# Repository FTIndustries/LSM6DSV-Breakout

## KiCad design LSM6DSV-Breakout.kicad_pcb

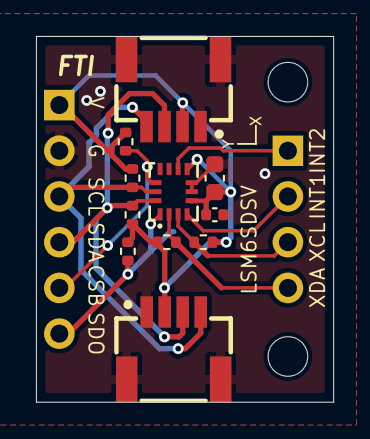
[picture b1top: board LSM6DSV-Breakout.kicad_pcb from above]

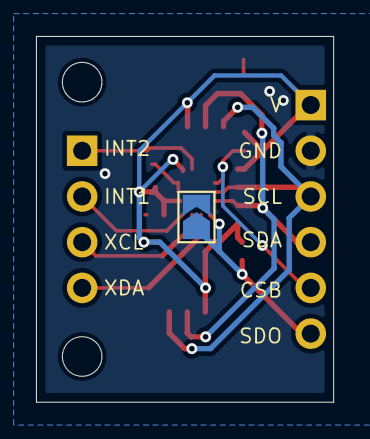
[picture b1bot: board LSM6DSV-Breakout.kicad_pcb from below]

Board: 2 copper layers, 16.5 x 20.3 mm, 16 parts (3 on the bottom side), 10 nets.

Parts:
C1: 1u; C_0603_1608Metric
C2: 100n; C_0402_1005Metric
CN1, CN2: AFC10-S04QCA-00; CONN-SMD_AFC10-S04QCA-00
H1, H2: MountingHole; MountingHole_2.2mm_M2
J1: Conn_01x06_Pin; PinHeader_1x06_P2.54mm_Vertical
J2: Conn_01x04_Pin; PinHeader_1x04_P2.54mm_Vertical
JP1: SolderJumper_2_Open; SolderJumper-2_P1.3mm_Open_TrianglePad1.0x1.5mm
R1, R2, R3, R4, R5, R6: 2.2k; R_0402_1005Metric
U1: LSM6DSVTR; LGA-14_L3.0-W2.5-P0.50-TL

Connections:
/CS: J1.5, R1.2, U1.12 (CS)
/INT1: J2.2, U1.4 (INT1)
/INT2: J2.1, U1.9 (INT2)
/SA0: J1.6, JP1.1 (A), R2.2, U1.1 (SDO/SA0)
/SCL: CN1.4, CN2.4, J1.3, R4.2, U1.13 (SCL)
/SDA: CN1.3, CN2.3, J1.4, R3.2, U1.14 (SDA)
/XCL: J2.3, R6.2, U1.3 (SCX)
/XDA: J2.4, R5.2, U1.2 (SDX)
GND: C1.2, C2.2, CN1.1, CN1.5, CN1.6, CN2.1, CN2.5, CN2.6, J1.2, JP1.2 (B), U1.6 (GND), U1.7 (GND)
VDD: C1.1, C2.1, CN1.2, CN2.2, J1.1, R1.1, R2.1, R3.1, R4.1, R5.1, R6.1, U1.5 (VDD_IO), U1.8 (VDD)

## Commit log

2024-04-23 add heading mark
2024-04-23 Unified 6DoF IMU footprint
2024-04-25 hide ref
2024-05-10 gitignore
2024-09-19 exclude 3dmodels
2024-09-19 redo silkscreen
2024-12-02 use higher pullup, make dippable
